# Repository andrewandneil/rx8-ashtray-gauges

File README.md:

# Mazda RX-8 Ashtray Gauges

As someone who likes knowing the vitals of my ever-so-fragile rotary engine, I wanted a way to monitor Oil Temperature, Oil Pressure, Coolant Temperature and Electrical System Voltage without needing big aftermarket gauges. I stumbled across Stephane Gilbert's work, where he built a small gauge system for coolant temperature, pressure and battery voltage, but it wasn't a perfect fit for me. I decided to take his basis, and modify it to my need. After several months of toiling around, I have finally produced this:

This project doesn't use the OBDII port, instead relying on deidcated sensors. For both oil and coolant temperature AEM-30-2012 sensors were used and for oil pressure a 200 PSI pressure transducer was used. Electrical system voltage is calculated using the supplied power on board.

The design uses two PCBs, one PCB that houses the electronics, and another PCB inside the ashtray cavity to breakout the connectors for screens and sensors.

## Features
- Coolant Temperature Monitoring & Warning.
- Oil Temperature and Pressure Monitoring & Warning.
- System Voltage Monitoring & Warning.
- Screen auto-off when ashtray lid is closed.
- Optional LED warning lights when temperature, pressure or voltage is out of user specified limits.
- Optional buzzer sound when temperature, pressure or voltage is out of user specified limits. [NOT IMPLEMENTED ATM]

## Sensors
If you're building this yourself, this is where you can go your own route, you may prefer to use the oil filter sandwich plate, in which case disregard anything below. You also shouldnt need a 200 PSI sensor if you're using the sandwich plate, a 100 PSI sensor would be more appropriate (do your own research, this is what I've found searching around). You may also prefer to add your coolant temp sensor to the main radiator hose, in which case of course there are guides out there for that.

#### My Oil Temperature Sensor Location:
A modified banjo bolt with a 1/8NPT thread cut into the top is used. Add thread sealant to the NPT threads and not to the banjo bolt threads (that's what the crush washers are for). Mounted to the banjo bolt on the front passanger side oil cooler.

#### My Oil Pressure Sensor Location:
A modified banjo bolt with a 1/8NPT thread cut into the top is used. Add thread sealant to the NPT threads and not to the banjo bolt threads (that's what the crush washers are for). Mounted to the banjo bolt on the feed line to the oil cooler.

#### My Coolant Temperature Sensor Location:
A Racing Beat RX-8 Water Temp Sensor Hose Adapter is used with a 3/8 to 1/8 step down adapter to fit the 1/8NPT thread of the sensor. Add thread sealant to the threads on both the adapter and sensor. Fitted to the heater core hose located on the passanger side.

## 3D Printing
The cases for the electronics and the OLED screen holders are designed to be 3D printed by a standard FDM printer. 

### Electronics Housing
Recommended print settings:
- PETG or ABS/ASA (don't use PLA as it will warp when exposed to the sun or heat)
- 0.2mm Layer Height

You'll also need:
- x6 M3 Heat set inserts (OD: 4mm, Length: 4.2mm)
- x6 M3x10 Bolts
- x2 M3 Washers (for clamping the CPT power item to the board)

### OLED Screen Holder
Recommended print settings:
- PETG or ABS/ASA (don't use PLA as it will warp when exposed to the sun or heat)
- 0.1mm or 0.15mm Layer Height

You'll also need:
- x5 M3 Heat set inserts (OD: 4mm, Length: 4.2mm)
- x2 M3x10 Bolts
- x3 M3x4 Bolts

### OLED Screen Spacers
Print two, one for each oled screen.

Recommended print settings:
- PETG or ABS/ASA (don't use PLA as it will warp when exposed to the sun or heat)
- 0.2mm Layer Height

You'll also need:
- x8 M2.5x8 Dome Head Bolts (must be low profile)
- x8 M2.5 Nuts
- x8 M2.5 Washers

## Useful Links
A guide for adding the oil temperature and pressure sensors: https://www.rx8club.com/series-i-do-yourself-forum-73/diy-oil-temp-pressure-sender-install-modified-banjo-bolts-235867/

rx8-coolant-monitor by Stephane Gilbert (topolittle): https://github.com/topolittle/rx8-coolant-monitor

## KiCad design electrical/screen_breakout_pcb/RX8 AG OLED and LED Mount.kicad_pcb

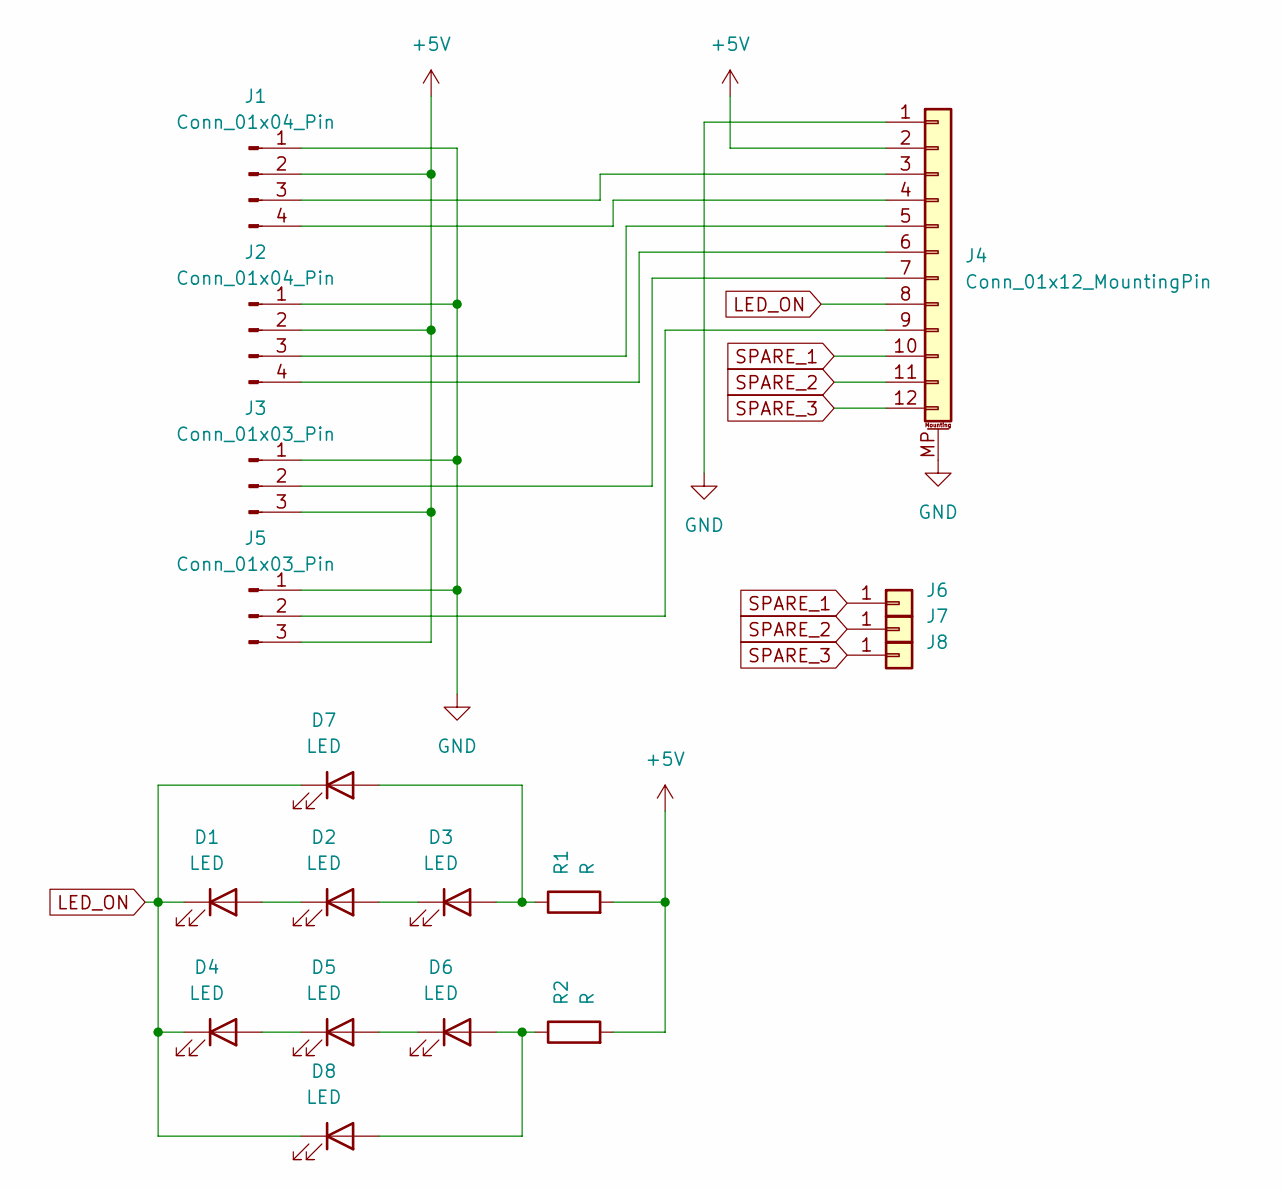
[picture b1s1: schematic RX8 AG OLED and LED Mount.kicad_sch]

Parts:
D1, D2, D3, D4, D5, D6: LED; LED_0805_2012Metric
D7, D8: LED; LED_D5.0mm
J1, J2: Conn_01x04_Pin; PinHeader_1x04_P2.54mm_Vertical
J3, J5: Conn_01x03_Pin; PinHeader_1x03_P2.54mm_Vertical_SMD_Pin1Left
J4: Conn_01x12_MountingPin; JST_PH_B12B-PH-SM4-TB_1x12-1MP_P2.00mm_Vertical
J6, J7, J8: Conn_01x01; SolderWirePad_1x01_SMD_1x2mm
R1, R2: R; R_0805_2012Metric_Pad1.20x1.40mm_HandSolder

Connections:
+5V: J1.2, J2.2, J3.3, J4.2, J5.3, R1.2, R2.2
GND: J1.1, J2.1, J3.1, J4.1, J4.MP (MountPin), J5.1
LED_ON: D1.1 (K), D4.1 (K), D7.1 (K), D8.1 (K), J4.8
unnamed: D1.2 (A), D2.1 (K)
unnamed: D2.2 (A), D3.1 (K)
unnamed: D3.2 (A), D7.2 (A), R1.1
unnamed: D4.2 (A), D5.1 (K)
unnamed: D5.2 (A), D6.1 (K)
unnamed: D6.2 (A), D8.2 (A), R2.1
unnamed: J1.3, J4.3
unnamed: J1.4, J4.4
unnamed: J2.3, J4.5
unnamed: J2.4, J4.6
unnamed: J3.2, J4.7
unnamed: J4.9, J5.2
SPARE_1: J4.10, J6.1
SPARE_2: J4.11, J7.1
SPARE_3: J4.12, J8.1

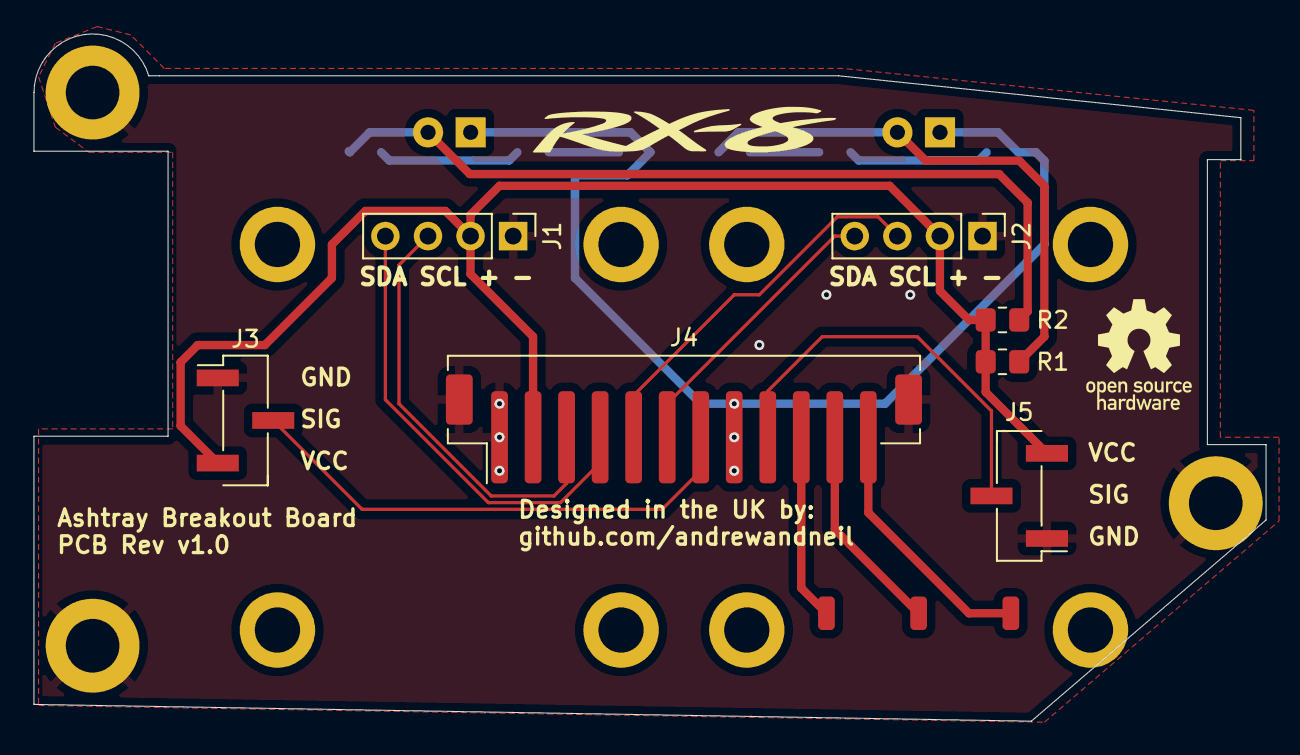
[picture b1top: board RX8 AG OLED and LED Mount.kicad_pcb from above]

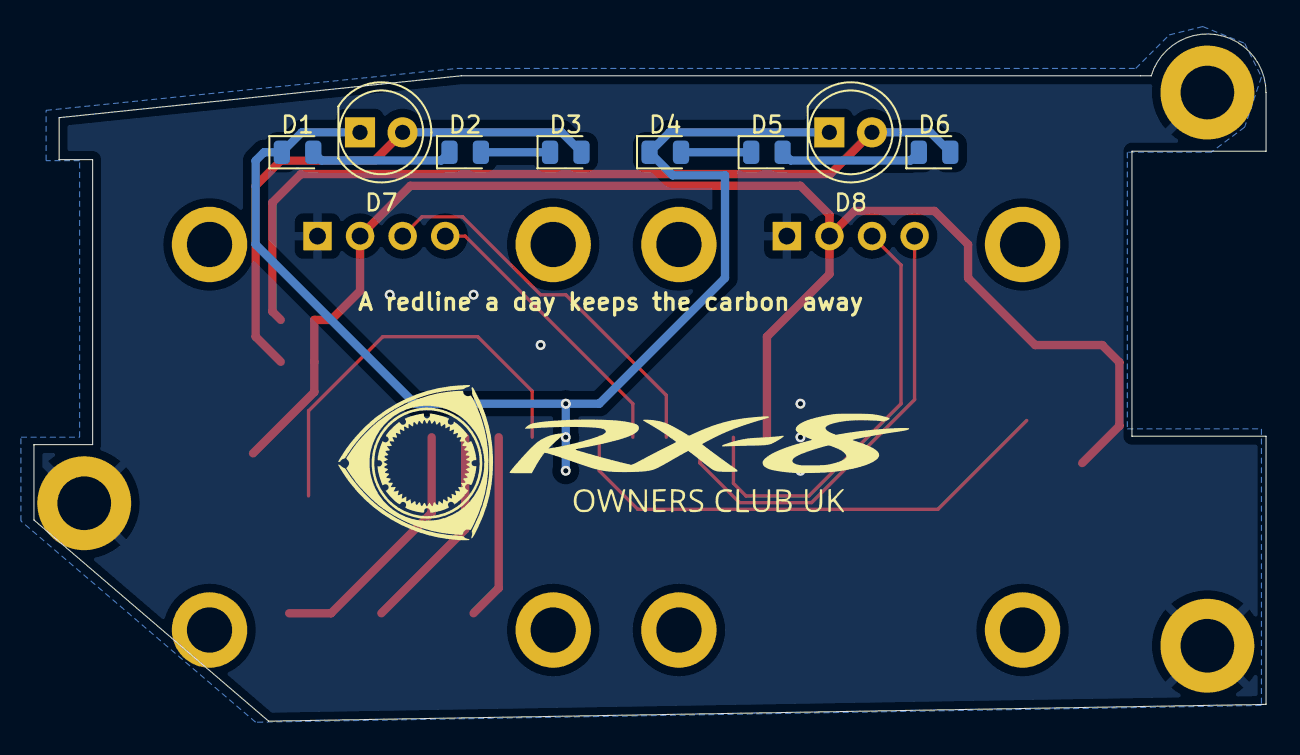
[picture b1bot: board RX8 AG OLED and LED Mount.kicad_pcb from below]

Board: 2 copper layers, 73.5 x 41.0 mm, 18 parts (8 on the bottom side), 18 nets.

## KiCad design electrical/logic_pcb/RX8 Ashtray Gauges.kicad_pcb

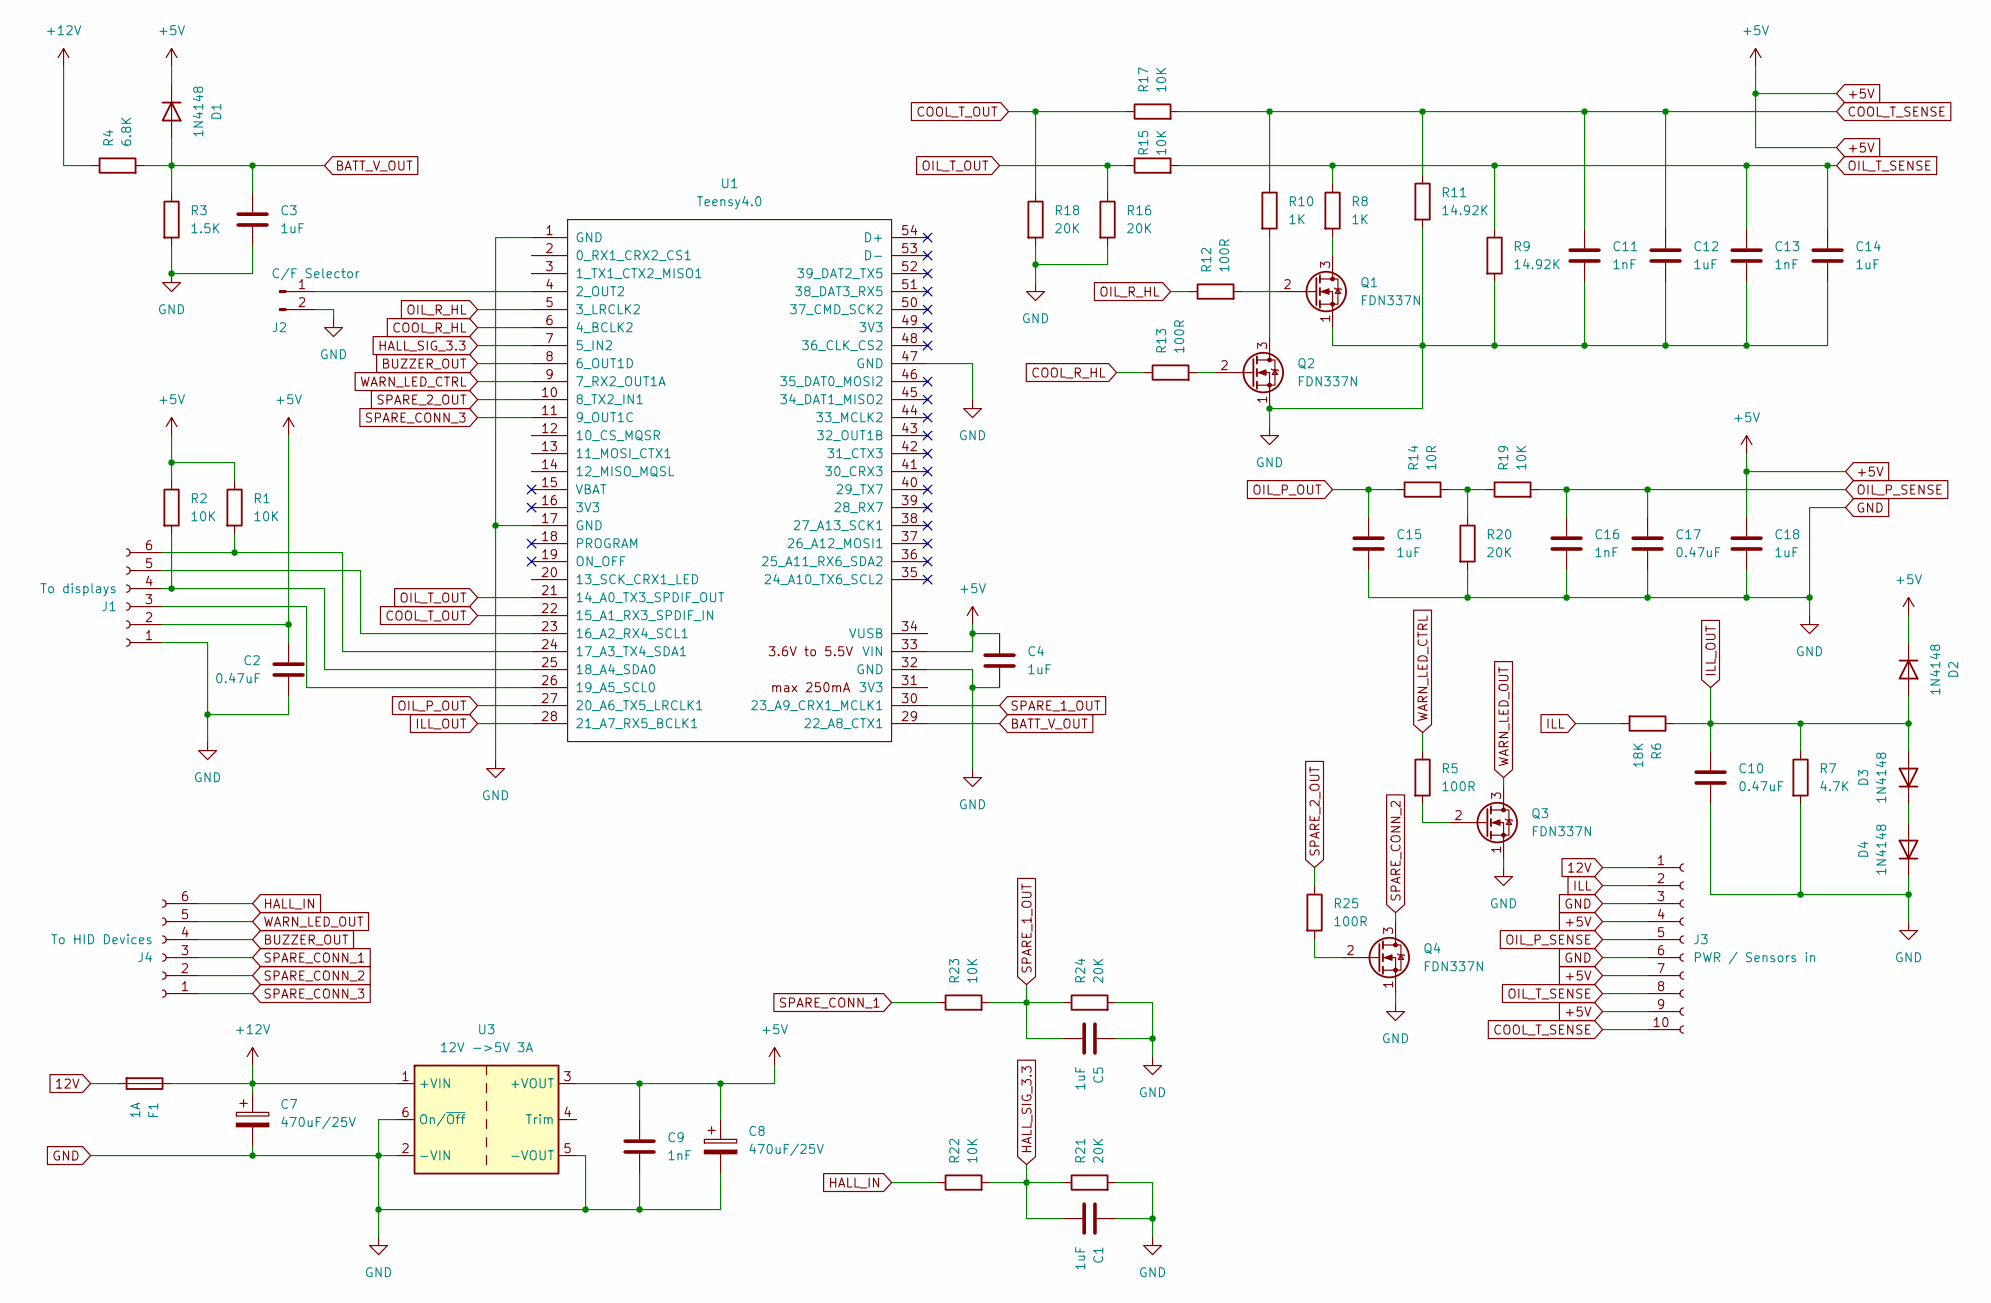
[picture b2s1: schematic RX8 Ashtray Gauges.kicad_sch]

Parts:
C1, C3, C4, C5, C12, C14, C15, C18: 1uF; C_Disc_D5.0mm_W2.5mm_P5.00mm
C2, C10, C17: 0.47uF; C_Disc_D5.0mm_W2.5mm_P5.00mm
C7, C8: 470uF/25V; CP_Radial_D8.0mm_P3.80mm
C9, C11, C13, C16: 1nF; C_Disc_D5.0mm_W2.5mm_P5.00mm
D1, D2, D3, D4: 1N4148; D_A-405_P7.62mm_Horizontal
F1: 1A; R_Axial_DIN0207_L6.3mm_D2.5mm_P10.16mm_Horizontal
J1: To displays; Molex_Mini-Fit_Jr_5569-06A2_2x03_P4.20mm_Horizontal
J2: C/F Selector; PinHeader_1x02_P2.54mm_Vertical
J3: PWR / Sensors in; Molex_Mini-Fit_Jr_5569-10A2_2x05_P4.20mm_Horizontal
J4: To HID Devices; Molex_Mini-Fit_Jr_5569-06A2_2x03_P4.20mm_Horizontal
Q1, Q2, Q3, Q4: FDN337N; SuperSOT-3
R1, R2, R15, R17, R19, R22, R23: 10K; R_Axial_DIN0207_L6.3mm_D2.5mm_P10.16mm_Horizontal
R3: 1.5K; R_Axial_DIN0207_L6.3mm_D2.5mm_P10.16mm_Horizontal
R4: 6.8K; R_Axial_DIN0207_L6.3mm_D2.5mm_P10.16mm_Horizontal
R5, R12, R13, R25: 100R; R_Axial_DIN0207_L6.3mm_D2.5mm_P10.16mm_Horizontal
R6: 18K; R_Axial_DIN0207_L6.3mm_D2.5mm_P10.16mm_Horizontal
R7: 4.7K; R_Axial_DIN0207_L6.3mm_D2.5mm_P10.16mm_Horizontal
R8, R10: 1K; R_Axial_DIN0207_L6.3mm_D2.5mm_P10.16mm_Horizontal
R9, R11: 14.92K; R_Axial_DIN0207_L6.3mm_D2.5mm_P10.16mm_Horizontal
R14: 10R; R_Axial_DIN0207_L6.3mm_D2.5mm_P10.16mm_Horizontal
R16, R18, R20, R21, R24: 20K; R_Axial_DIN0207_L6.3mm_D2.5mm_P10.16mm_Horizontal
U1: Teensy4.0; Teensy40_Simplified
U3: 12V ->5V 3A; CPT 7-12V to 5V DCDC Converter

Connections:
12V: F1.2, J3.1
+5V: C2.1, C4.1, C8.1, C9.1, C18.1, D1.1 (K), D2.1 (K), J1.2, J3.4, J3.7, J3.9, R1.1, R2.1, U1.33 (VIN), U3.3 (+VOUT)
+12V: C7.1, F1.1, R4.1, U3.1 (+VIN)
BATT_V_OUT: C3.1, D1.2 (A), R3.1, R4.2, U1.29 (22_A8_CTX1)
BUZZER_OUT: J4.4, U1.8 (6_OUT1D)
COOL_R_HL: R13.1, U1.6 (4_BCLK2)
COOL_T_OUT: R17.1, R18.1, U1.22 (15_A1_RX3_SPDIF_IN)
COOL_T_SENSE: C11.1, C12.1, J3.10, R10.1, R11.1, R17.2
GND: C1.1, C2.2, C3.2, C4.2, C5.1, C7.2, C8.2, C9.2, C10.2, C11.2, C12.2, C13.2, C14.2, C15.2, C16.2, C17.2, C18.2, D4.1 (K), J1.1, J2.2, J3.3, J3.6, Q1.1 (S), Q2.1 (S), Q3.1 (S), Q4.1 (S), R3.2, R7.2, R9.2, R11.2, R16.2, R18.2, R20.2, R21.2, R24.2, U1.1 (GND), U1.17 (GND), U1.32 (GND), U1.47 (GND), U3.2 (-VIN), U3.5 (-VOUT), U3.6 (On/~Off); also elsewhere on the board
HALL_IN: J4.6, R22.1
HALL_SIG_3.3: C1.2, R21.1, R22.2, U1.7 (5_IN2)
ILL: J3.2, R6.2
ILL_OUT: C10.1, D2.2 (A), D3.2 (A), R6.1, R7.1, U1.28 (21_A7_RX5_BCLK1)
unnamed: D3.1 (K), D4.2 (A)
unnamed: J1.3, U1.26 (19_A5_SCL0)
unnamed: J1.4, R2.2, U1.25 (18_A4_SDA0)
unnamed: J1.5, U1.23 (16_A2_RX4_SCL1)
unnamed: J1.6, R1.2, U1.24 (17_A3_TX4_SDA1)
unnamed: J2.1, U1.4 (2_OUT2)
unnamed: Q1.3 (D), R8.2
unnamed: Q1.2 (G), R12.2
unnamed: Q2.3 (D), R10.2
unnamed: Q2.2 (G), R13.2
unnamed: Q3.2 (G), R5.2
unnamed: Q4.2 (G), R25.2
unnamed: R14.2, R19.1, R20.1
OIL_P_OUT: C15.1, R14.1, U1.27 (20_A6_TX5_LRCLK1)
OIL_P_SENSE: C16.1, C17.1, J3.5, R19.2
OIL_R_HL: R12.1, U1.5 (3_LRCLK2)
OIL_T_OUT: R15.1, R16.1, U1.21 (14_A0_TX3_SPDIF_OUT)
OIL_T_SENSE: C13.1, C14.1, J3.8, R8.1, R9.1, R15.2
SPARE_1_OUT: C5.2, R23.2, R24.1, U1.30 (23_A9_CRX1_MCLK1)
SPARE_2_OUT: R25.1, U1.10 (8_TX2_IN1)
SPARE_CONN_1: J4.3, R23.1
SPARE_CONN_2: J4.2, Q4.3 (D)
SPARE_CONN_3: J4.1, U1.11 (9_OUT1C)
WARN_LED_CTRL: R5.1, U1.9 (7_RX2_OUT1A)
WARN_LED_OUT: J4.5, Q3.3 (D)

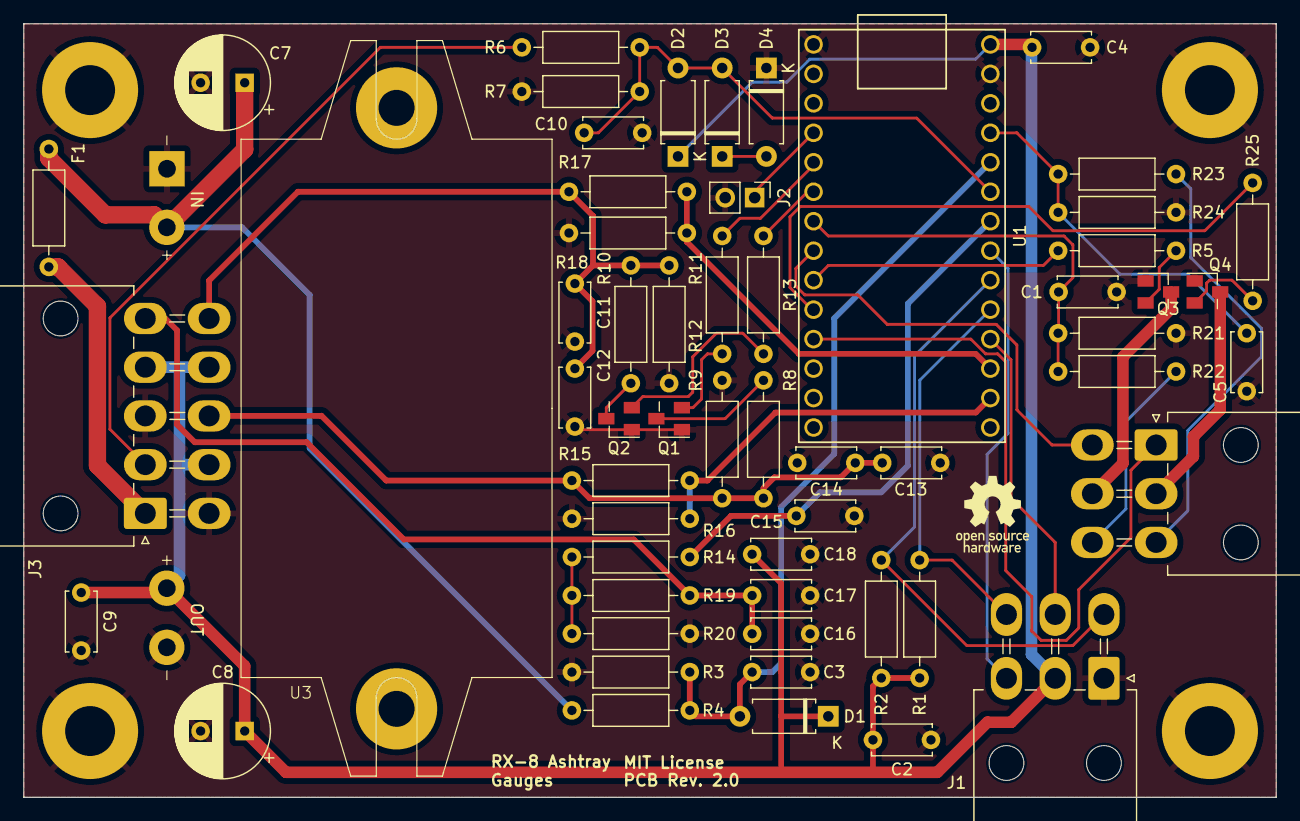
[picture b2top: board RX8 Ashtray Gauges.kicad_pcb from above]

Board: 2 copper layers, 108.0 x 66.7 mm, 61 parts (0 on the bottom side), 38 nets.

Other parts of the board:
J5, J6, J7, J8: Conn_01x01; Pin_D1.0mm_L10.0mm

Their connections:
GND: J5.1, J6.1, J7.1, J8.1; also elsewhere on the board

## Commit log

2024-06-03 added images
2024-06-03 fixed image link
2024-06-03 actually fixed image link
2024-06-12 Updated code and README
2024-06-12 added license
2024-06-23 updated readme and added photos, changed pressure code
2024-06-23 fixed incorrect image link

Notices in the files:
electrical/logic_pcb/RX8 Ashtray Gauges.kicad_pcb:
MIT License
